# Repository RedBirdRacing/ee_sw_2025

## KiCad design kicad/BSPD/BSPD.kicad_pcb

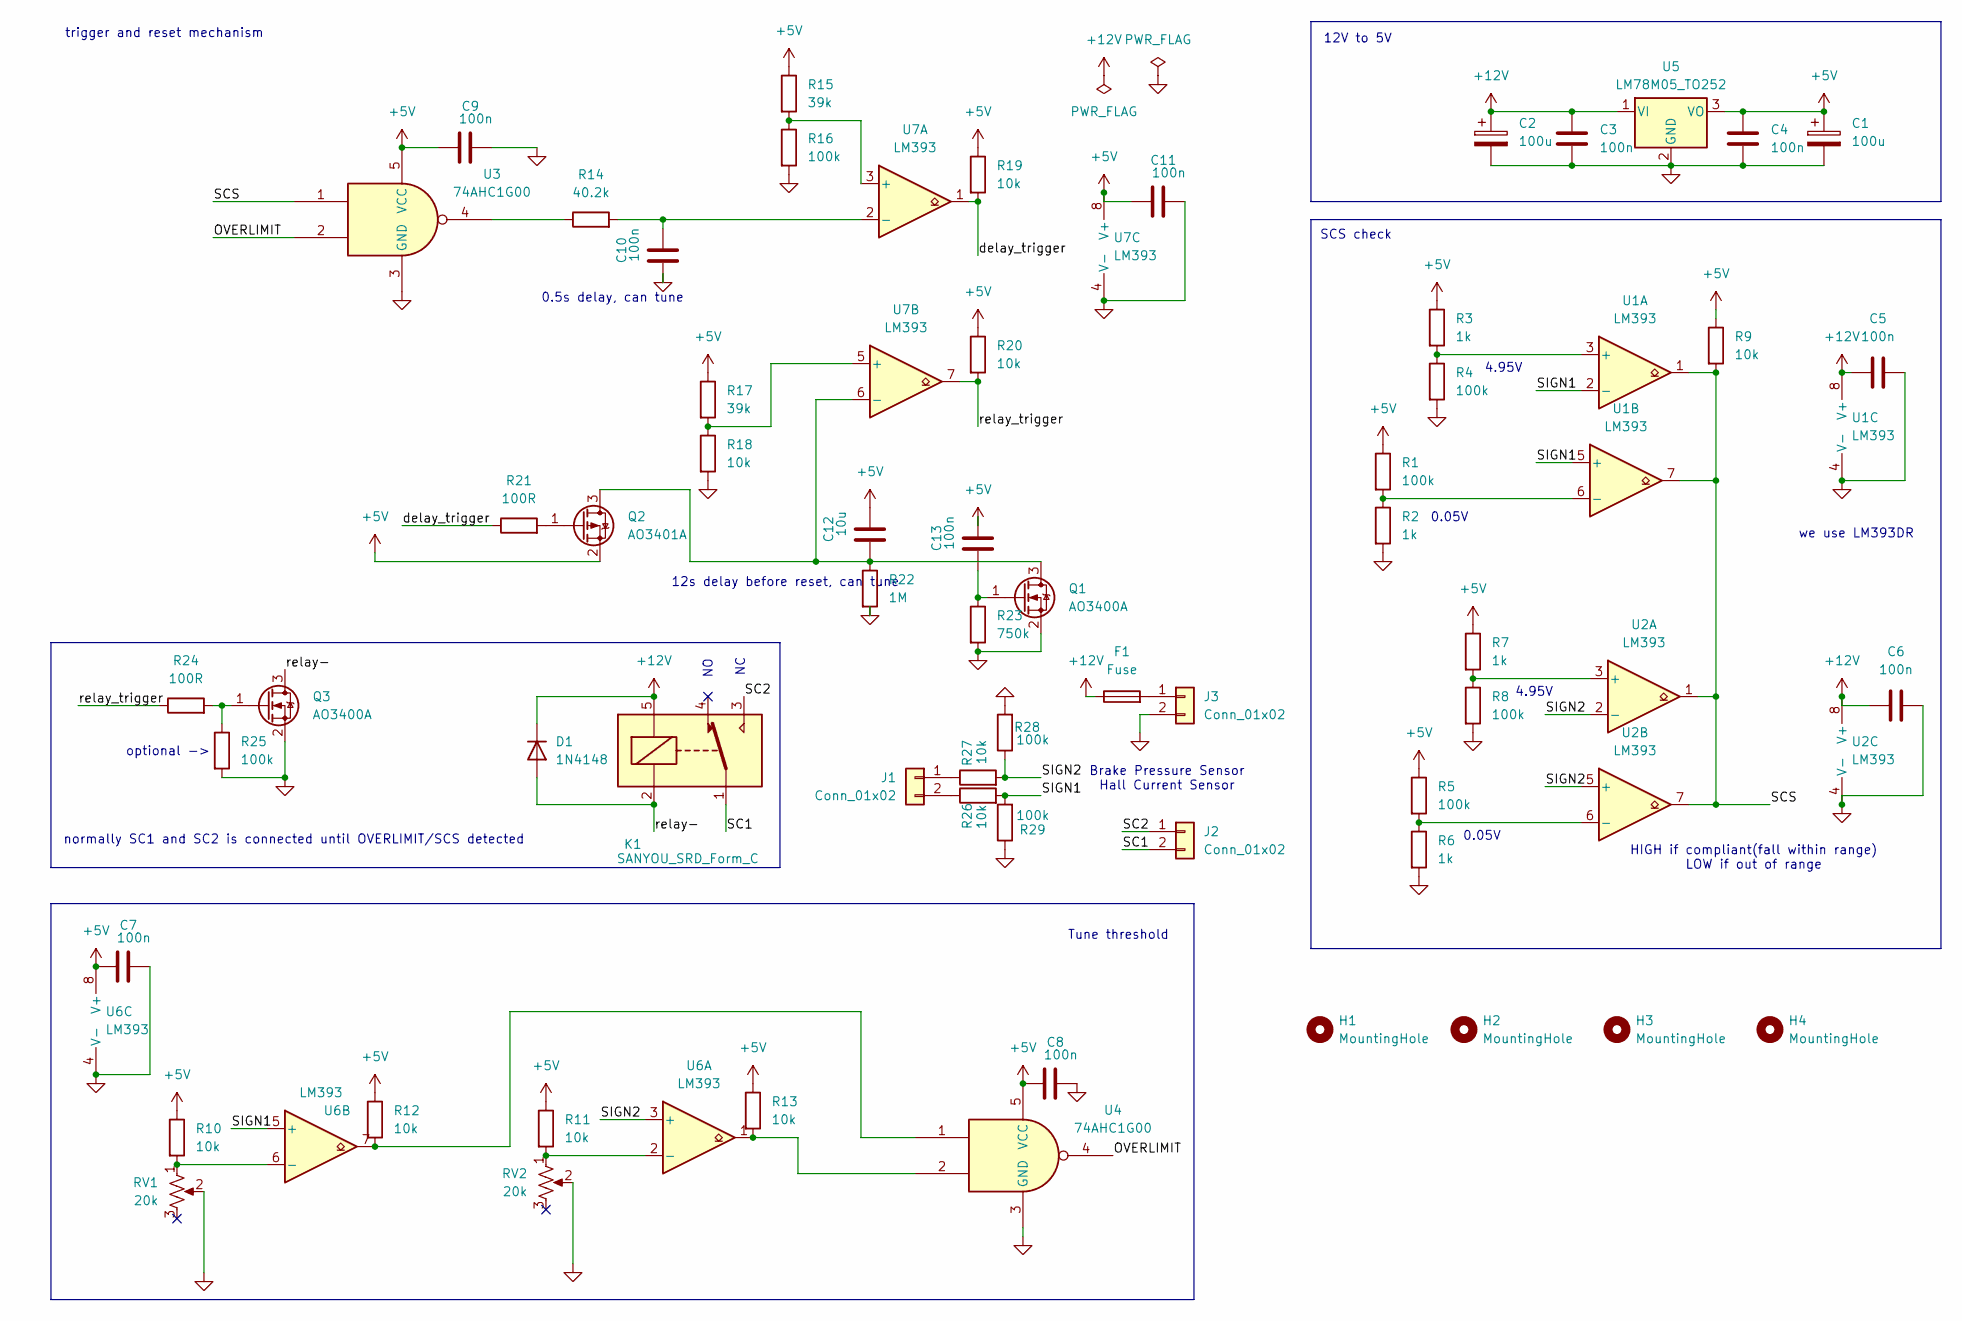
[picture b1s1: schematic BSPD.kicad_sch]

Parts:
C1, C2: 100u; CP_Radial_D5.0mm_P2.50mm
C3, C4, C5, C6, C7, C8, C9, C10, C11, C13: 100n; C_0805_2012Metric_Pad1.18x1.45mm_HandSolder
C12: 10u; C_0805_2012Metric_Pad1.18x1.45mm_HandSolder
D1: 1N4148; D_DO-35_SOD27_P7.62mm_Horizontal
F1: Fuse; Fuse_0805_2012Metric_Pad1.15x1.40mm_HandSolder
H1, H2, H3, H4: MountingHole; MountingHole_3.2mm_M3
J1, J2, J3: Conn_01x02; Molex_Micro-Fit_3.0_43650-0215_1x02_P3.00mm_Vertical
K1: SANYOU_SRD_Form_C; Relay_SPDT_SANYOU_SRD_Series_Form_C
Q1, Q3: AO3400A; SOT-23
Q2: AO3401A; SOT-23
R1, R4, R5, R8, R16, R25, R28, R29: 100k; R_0805_2012Metric_Pad1.20x1.40mm_HandSolder
R2, R3, R6, R7: 1k; R_0805_2012Metric_Pad1.20x1.40mm_HandSolder
R9, R10, R11, R12, R13, R18, R19, R20, R26, R27: 10k; R_0805_2012Metric_Pad1.20x1.40mm_HandSolder
R14: 40.2k; R_0805_2012Metric_Pad1.20x1.40mm_HandSolder
R15, R17: 39k; R_0805_2012Metric_Pad1.20x1.40mm_HandSolder
R21, R24: 100R; R_0805_2012Metric_Pad1.20x1.40mm_HandSolder
R22: 1M; R_0805_2012Metric_Pad1.20x1.40mm_HandSolder
R23: 750k; R_0805_2012Metric_Pad1.20x1.40mm_HandSolder
RV1, RV2: 20k; Potentiometer_Bourns_3296W_Vertical
U1, U2, U6, U7: LM393; SOIC-8_3.9x4.9mm_P1.27mm
U3, U4: 74AHC1G00; SOT-23-5_HandSoldering
U5: LM78M05_TO252; TO-252-2

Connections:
+5V: C1.1, C4.1, C7.1, C8.1, C9.1, C11.1, C12.2, C13.2, Q2.2 (S), R1.1, R3.1, R5.1, R7.1, R9.1, R10.1, R11.1, R12.1, R13.1, R15.1, R17.1, R19.1, R20.1, U3.5 (VCC), U4.5 (VCC), U5.3 (VO), U6.8 (V+), U7.8 (V+)
+12V: C2.1, C3.1, C5.1, C6.1, D1.1 (K), F1.1, K1.5, U1.8 (V+), U2.8 (V+), U5.1 (VI)
/OVERLIMIT: U3.2, U4.4
/SC1: J2.2, K1.1
/SC2: J2.1, K1.3
/SCS: R9.2, U1.1, U1.7, U2.1, U2.7, U3.1
/SIGN1: R26.2, R29.2, U1.2 (-), U1.5 (+), U6.5 (+)
/SIGN2: R27.2, R28.1, U2.2 (-), U2.5 (+), U6.3 (+)
/delay_trigger: R19.2, R21.1, U7.1
/relay-: D1.2 (A), K1.2, Q3.3 (D)
/relay_trigger: R20.2, R24.1, U7.7
GND: C1.2, C2.2, C3.2, C4.2, C5.2, C6.2, C7.2, C8.2, C9.2, C10.1, C11.2, J3.2, Q1.2 (S), Q3.2 (S), R2.2, R4.2, R6.2, R8.2, R16.2, R18.2, R22.2, R23.2, R25.2, R28.2, R29.1, RV1.2, RV2.2, U1.4 (V-), U2.4 (V-), U3.3 (GND), U4.3 (GND), U5.2 (GND), U6.4 (V-), U7.4 (V-)
unnamed: J1.1, R27.1
unnamed: J1.2, R26.1
unnamed: F1.2, J3.1
unnamed: C12.1, Q1.3 (D), Q2.3 (D), R22.1, U7.6 (-)
unnamed: C13.1, Q1.1 (G), R23.1
unnamed: Q2.1 (G), R21.2
unnamed: Q3.1 (G), R24.2, R25.1
unnamed: R12.2, U4.1, U6.7
unnamed: R13.2, U4.2, U6.1
unnamed: R14.1, U3.4
unnamed: R3.2, R4.1, U1.3 (+)
unnamed: R1.2, R2.1, U1.6 (-)
unnamed: R7.2, R8.1, U2.3 (+)
unnamed: R5.2, R6.1, U2.6 (-)
unnamed: R11.2, RV2.1, U6.2 (-)
unnamed: R10.2, RV1.1, U6.6 (-)
unnamed: R15.2, R16.1, U7.3 (+)
unnamed: C10.2, R14.2, U7.2 (-)
unnamed: R17.2, R18.1, U7.5 (+)

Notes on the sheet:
4.95V
0.05V
Tune threshold
12s delay before reset, can tune
HIGH if compliant(fall within range) LOW if out of range
optional ->
0.5s delay, can tune
we use LM393DR
normally SC1 and SC2 is connected until OVERLIMIT/SCS detected
12V to 5V
SCS check
Brake Pressure Sensor Hall Current Sensor
trigger and reset mechanism

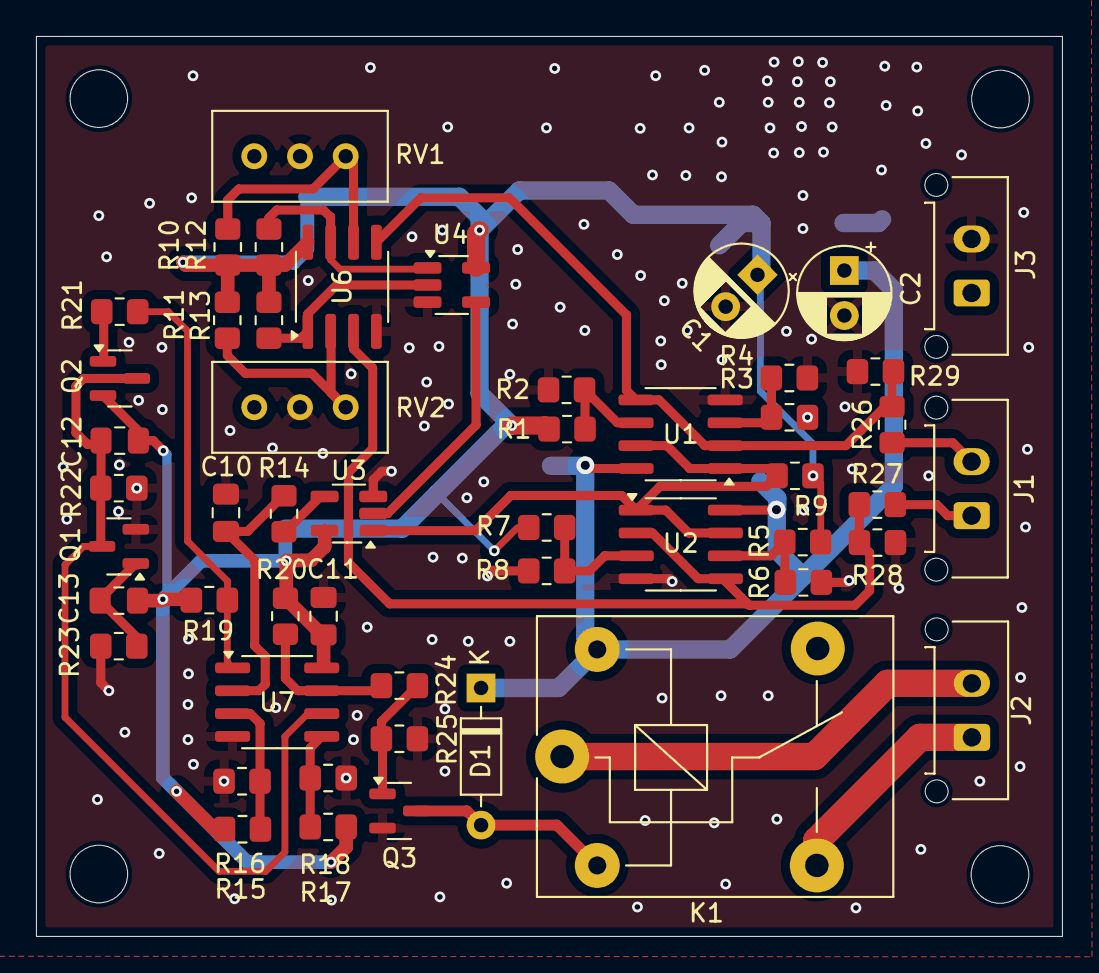
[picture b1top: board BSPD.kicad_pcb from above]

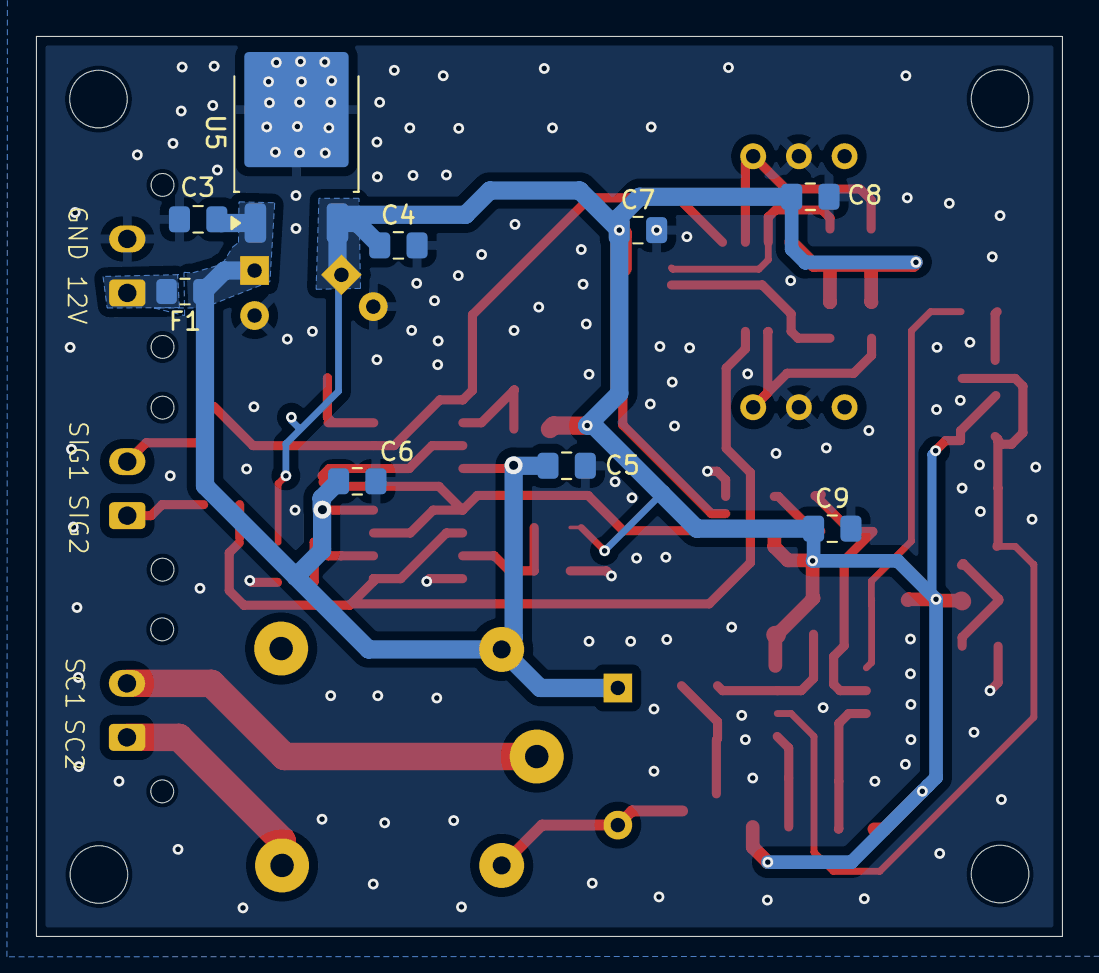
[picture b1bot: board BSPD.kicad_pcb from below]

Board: 2 copper layers, 57.0 x 50.0 mm, 64 parts (9 on the bottom side), 31 nets.

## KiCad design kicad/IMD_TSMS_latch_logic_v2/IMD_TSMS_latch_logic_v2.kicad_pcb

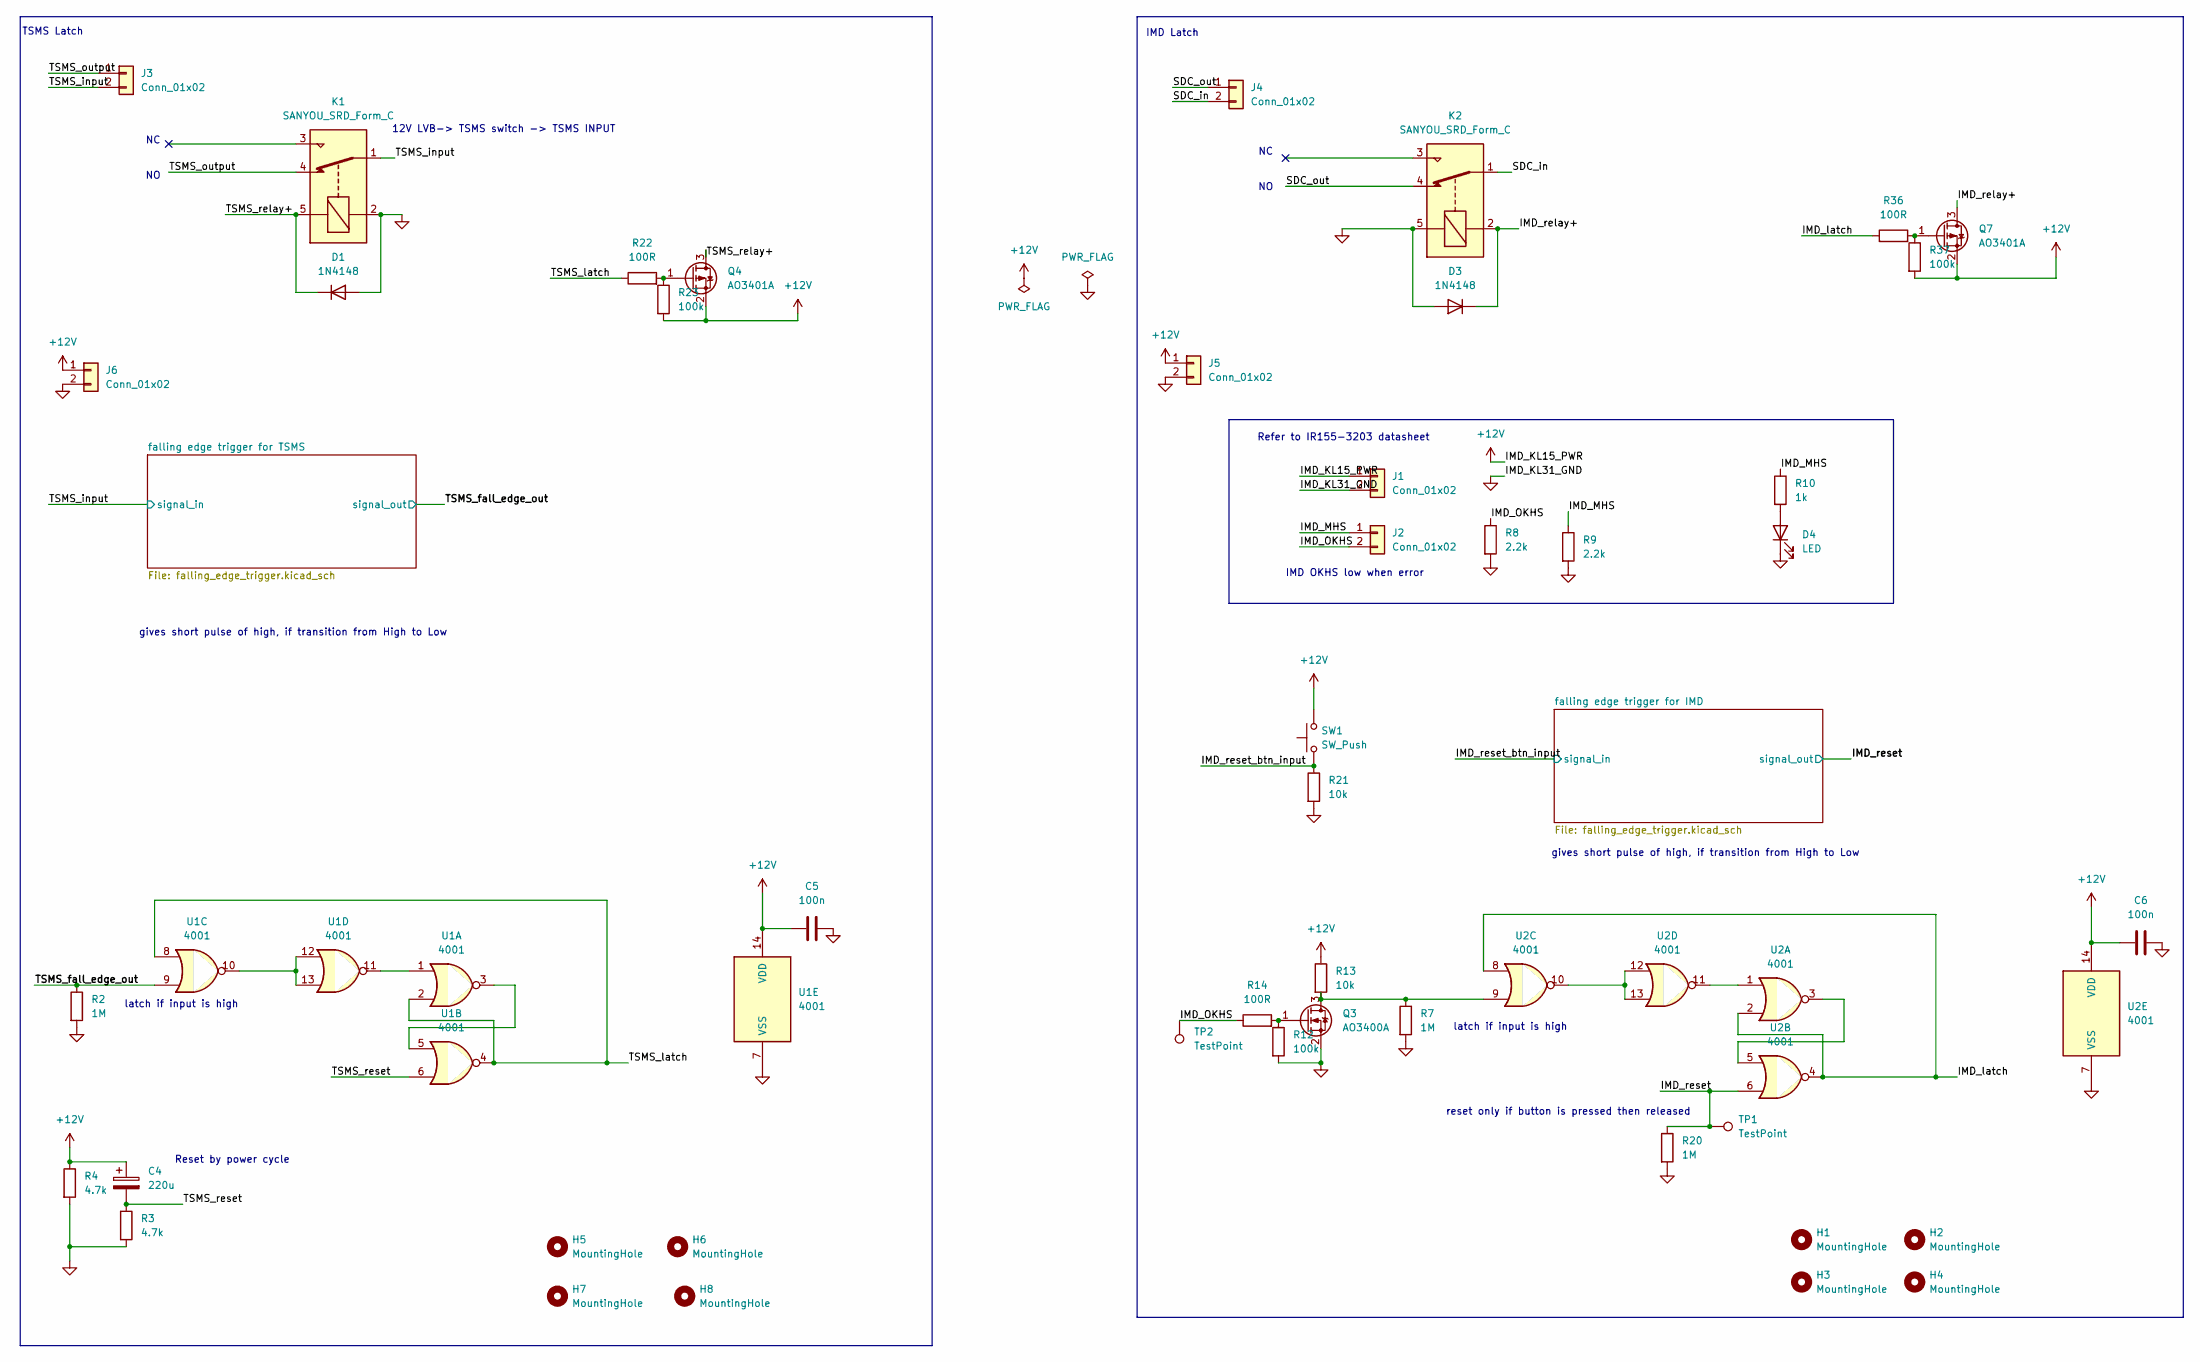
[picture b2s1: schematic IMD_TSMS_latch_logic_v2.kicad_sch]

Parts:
C4: 220u; CP_Radial_D5.0mm_P2.00mm
C5, C6: 100n; C_0805_2012Metric_Pad1.18x1.45mm_HandSolder
D1, D3: 1N4148; D_DO-35_SOD27_P7.62mm_Horizontal
D4: LED; LED_0805_2012Metric_Pad1.15x1.40mm_HandSolder
H1, H2, H3, H4, H5, H6, H7, H8: MountingHole; MountingHole_3.7mm
J1, J2, J3, J4, J5, J6: Conn_01x02; Molex_Micro-Fit_3.0_43650-0215_1x02_P3.00mm_Vertical
K1, K2: SANYOU_SRD_Form_C; Relay_SPDT_SANYOU_SRD_Series_Form_C
Q3: AO3400A; SOT-23
Q4, Q7: AO3401A; SOT-23
R2, R7, R20: 1M; R_0805_2012Metric_Pad1.20x1.40mm_HandSolder
R3, R4: 4.7k; R_0805_2012Metric_Pad1.20x1.40mm_HandSolder
R8, R9: 2.2k; R_0805_2012Metric_Pad1.20x1.40mm_HandSolder
R10: 1k; R_0805_2012Metric_Pad1.20x1.40mm_HandSolder
R12, R23, R37: 100k; R_0805_2012Metric_Pad1.20x1.40mm_HandSolder
R13, R21: 10k; R_0805_2012Metric_Pad1.20x1.40mm_HandSolder
R14, R22, R36: 100R; R_0805_2012Metric_Pad1.20x1.40mm_HandSolder
SW1: SW_Push; Molex_Micro-Fit_3.0_43650-0215_1x02_P3.00mm_Vertical
TP1, TP2: TestPoint; TestPoint_Bridge_Pitch2.54mm_Drill1.0mm
U1, U2: 4001; SOIC127P600X175-14N

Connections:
+12V: C4.1, C5.1, C6.1, J1.1, J5.1, J6.1, Q4.2 (S), Q7.2 (S), R4.1, R13.1, R23.2, R37.2, SW1.2, U1.14 (VDD), U2.14 (VDD); also elsewhere on the board
/IMD_MHS: J2.1, R9.1, R10.1
/IMD_OKHS: J2.2, R8.1, R14.1, TP2.1
/IMD_latch: R36.1, U2.2, U2.4, U2.8
/IMD_relay+: D3.1 (K), K2.2, Q7.3 (D)
/IMD_reset: R20.1, TP1.1, U2.6; also elsewhere on the board
/IMD_reset_btn_input: R21.1, SW1.1; also elsewhere on the board
/SDC_in: J4.2, K2.1
/SDC_out: J4.1, K2.4
/TSMS_fall_edge_out: R2.1, U1.9; also elsewhere on the board
/TSMS_input: J3.2, K1.1; also elsewhere on the board
/TSMS_latch: R22.1, U1.2, U1.4, U1.8
/TSMS_output: J3.1, K1.4
/TSMS_relay+: D1.1 (K), K1.5, Q4.3 (D)
/TSMS_reset: C4.2, R3.1, U1.6
GND: C5.2, C6.2, D1.2 (A), D3.2 (A), D4.1 (K), J1.2, J5.2, J6.2, K1.2, K2.5, Q3.2 (S), R2.2, R3.2, R4.2, R7.2, R8.2, R9.2, R12.2, R20.2, R21.2, U1.7 (VSS), U2.7 (VSS); also elsewhere on the board
unnamed: D4.2 (A), R10.2
unnamed: Q3.3 (D), R7.1, R13.2, U2.9
unnamed: Q3.1 (G), R12.1, R14.2
unnamed: Q4.1 (G), R22.2, R23.1
unnamed: Q7.1 (G), R36.2, R37.1
unnamed: U1.1, U1.11
unnamed: U1.3, U1.5
unnamed: U1.10, U1.12, U1.13
unnamed: U2.1, U2.11
unnamed: U2.3, U2.5
unnamed: U2.10, U2.12, U2.13

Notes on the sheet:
reset only if button is pressed then released
gives short pulse of high, if transition from High to Low
latch if input is high
IMD OKHS low when error
Refer to IR155-3203 datasheet
TSMS Latch
IMD Latch
Reset by power cycle
12V LVB-> TSMS switch -> TSMS INPUT

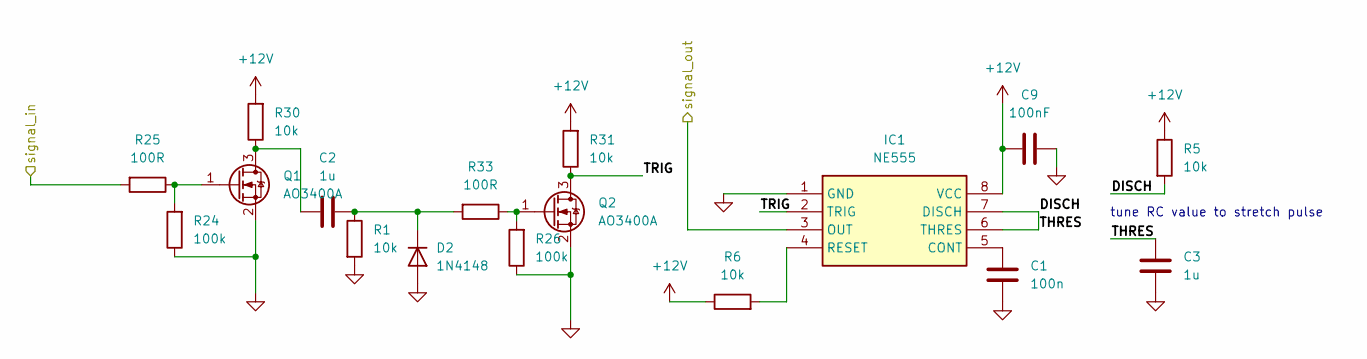
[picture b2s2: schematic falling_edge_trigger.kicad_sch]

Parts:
C1: 100n; C_0805_2012Metric_Pad1.18x1.45mm_HandSolder
C2, C3: 1u; C_0805_2012Metric_Pad1.18x1.45mm_HandSolder
C9: 100nF; C_0805_2012Metric_Pad1.18x1.45mm_HandSolder
D2: 1N4148; D_DO-35_SOD27_P7.62mm_Horizontal
IC1: NE555; SOIC-8_3.9x4.9mm_P1.27mm; Manufacturer_Part_Number NE555; Mouser Part Number N/A
Q1, Q2: AO3400A; SOT-23
R1, R5, R6, R30, R31: 10k; R_0805_2012Metric_Pad1.20x1.40mm_HandSolder
R24, R26: 100k; R_0805_2012Metric_Pad1.20x1.40mm_HandSolder
R25, R33: 100R; R_0805_2012Metric_Pad1.20x1.40mm_HandSolder

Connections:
+12V: C9.1, IC1.8 (VCC), R5.1, R6.1, R30.2, R31.2; also elsewhere on the board
/TSMS_fall_edge_out: IC1.3 (OUT); also elsewhere on the board
/TSMS_input: R25.2; also elsewhere on the board
/falling edge trigger for TSMS/DISCH: C3.1, IC1.6 (THRES), IC1.7 (DISCH), R5.2
/falling edge trigger for TSMS/TRIG: IC1.2 (TRIG), Q2.3 (D), R31.1
GND: C1.2, C3.2, C9.2, D2.2 (A), IC1.1 (GND), Q1.2 (S), Q2.2 (S), R1.2, R24.1, R26.1; also elsewhere on the board
unnamed: C2.2, D2.1 (K), R1.1, R33.2
unnamed: C1.1, IC1.5 (CONT)
unnamed: IC1.4 (RESET), R6.2
unnamed: C2.1, Q1.3 (D), R30.1
unnamed: Q1.1 (G), R24.2, R25.1
unnamed: Q2.1 (G), R26.2, R33.1

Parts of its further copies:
C7, C11: 1u; C_0805_2012Metric_Pad1.18x1.45mm_HandSolder
C8: 100n; C_0805_2012Metric_Pad1.18x1.45mm_HandSolder
C10: 100nF; C_0805_2012Metric_Pad1.18x1.45mm_HandSolder
D6: 1N4148; D_DO-35_SOD27_P7.62mm_Horizontal
IC2: NE555; SOIC-8_3.9x4.9mm_P1.27mm; Manufacturer_Part_Number NE555; Mouser Part Number N/A
Q5, Q6: AO3400A; SOT-23
R17, R18, R19, R32, R35: 10k; R_0805_2012Metric_Pad1.20x1.40mm_HandSolder
R27, R34: 100R; R_0805_2012Metric_Pad1.20x1.40mm_HandSolder
R28, R29: 100k; R_0805_2012Metric_Pad1.20x1.40mm_HandSolder

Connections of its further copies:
+12V: C10.1, IC2.8 (VCC), R18.1, R19.1, R32.2, R35.2; also elsewhere on the board
/IMD_reset: IC2.3 (OUT); also elsewhere on the board
/IMD_reset_btn_input: R27.2; also elsewhere on the board
/falling edge trigger for IMD/DISCH: C11.1, IC2.6 (THRES), IC2.7 (DISCH), R19.2
/falling edge trigger for IMD/TRIG: IC2.2 (TRIG), Q6.3 (D), R35.1
GND: C8.2, C10.2, C11.2, D6.2 (A), IC2.1 (GND), Q5.2 (S), Q6.2 (S), R17.2, R28.1, R29.1; also elsewhere on the board
unnamed: C7.2, D6.1 (K), R17.1, R34.2
unnamed: C8.1, IC2.5 (CONT)
unnamed: IC2.4 (RESET), R18.2
unnamed: C7.1, Q5.3 (D), R32.1
unnamed: Q5.1 (G), R27.1, R28.2
unnamed: Q6.1 (G), R29.2, R34.1

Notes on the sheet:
tune RC value to stretch pulse

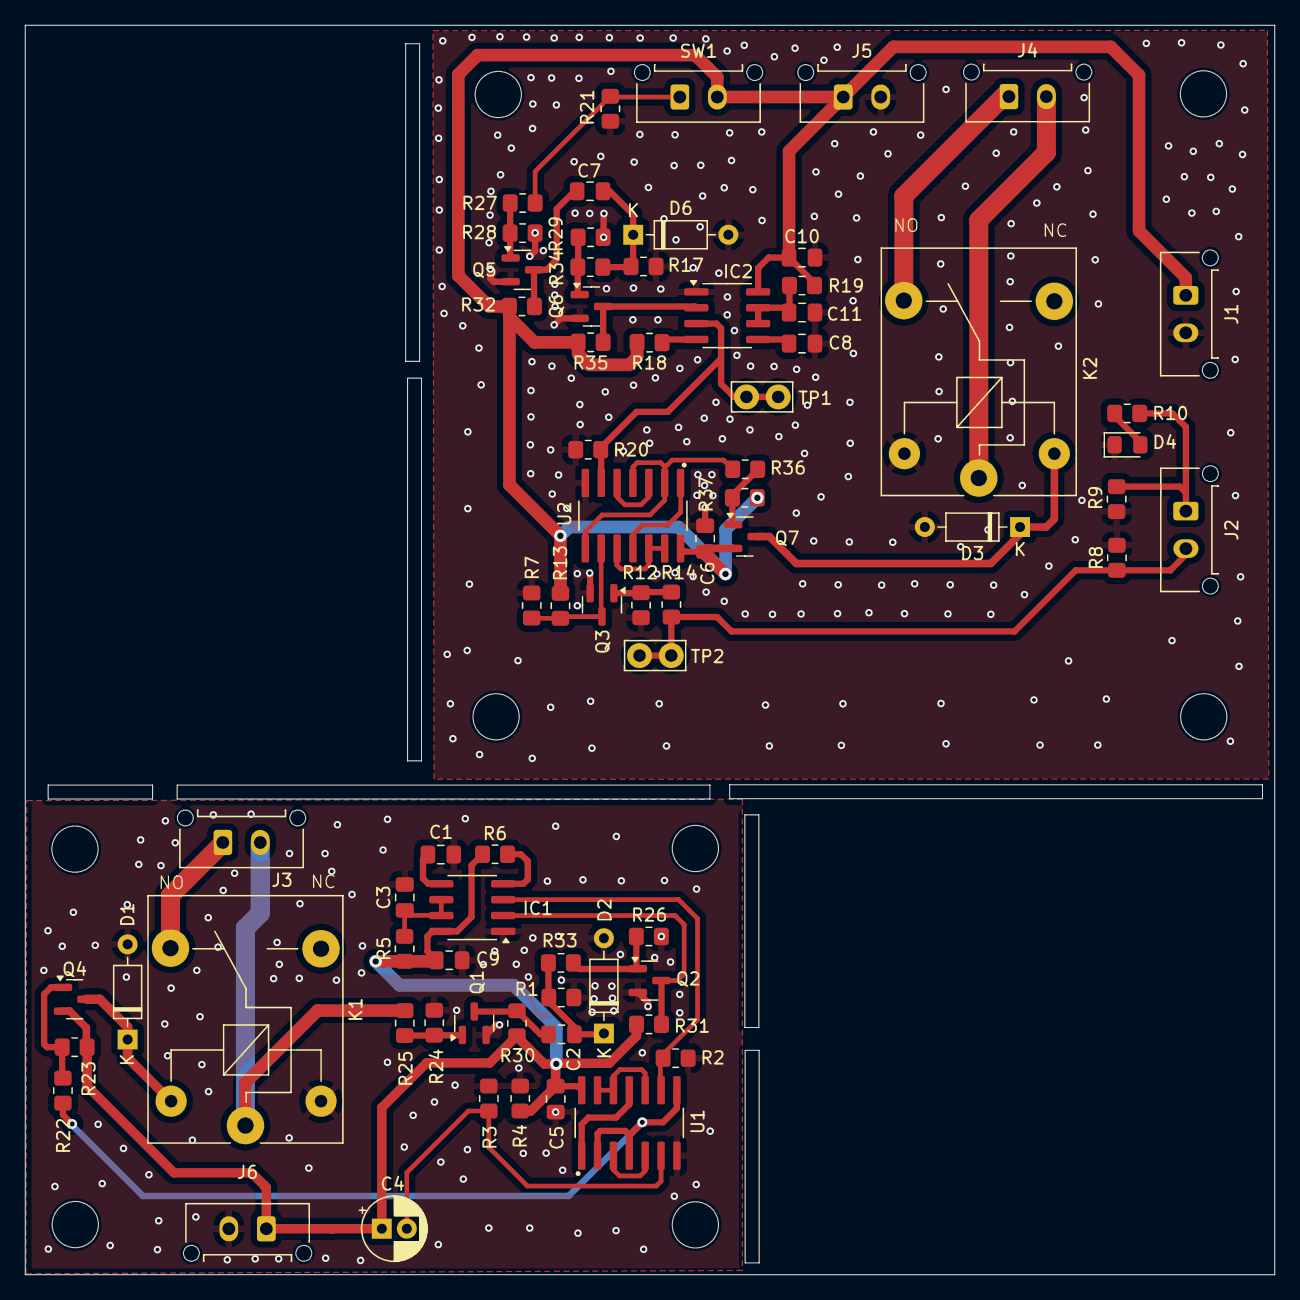
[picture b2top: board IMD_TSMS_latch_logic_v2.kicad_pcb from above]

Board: 2 copper layers, 100.0 x 100.0 mm, 80 parts (0 on the bottom side), 43 nets.
